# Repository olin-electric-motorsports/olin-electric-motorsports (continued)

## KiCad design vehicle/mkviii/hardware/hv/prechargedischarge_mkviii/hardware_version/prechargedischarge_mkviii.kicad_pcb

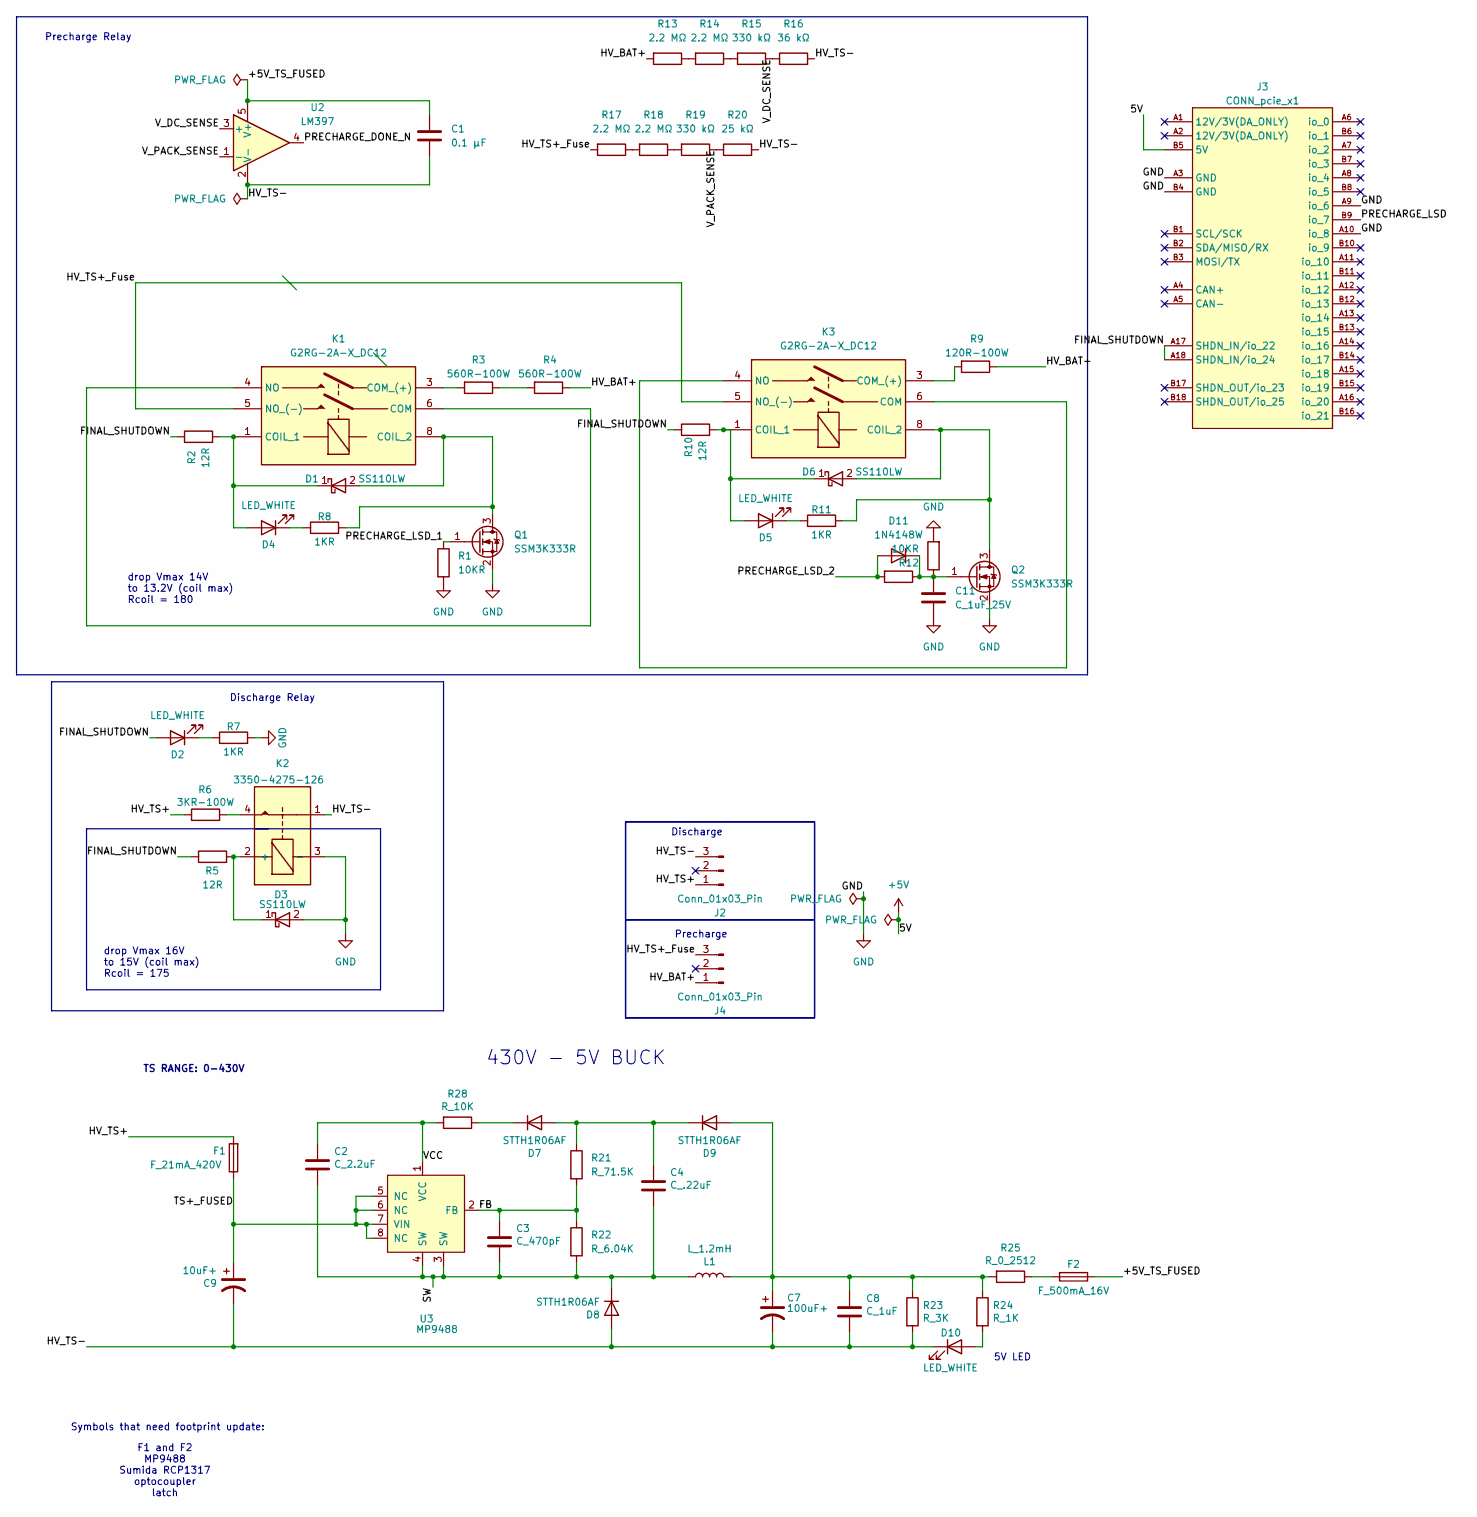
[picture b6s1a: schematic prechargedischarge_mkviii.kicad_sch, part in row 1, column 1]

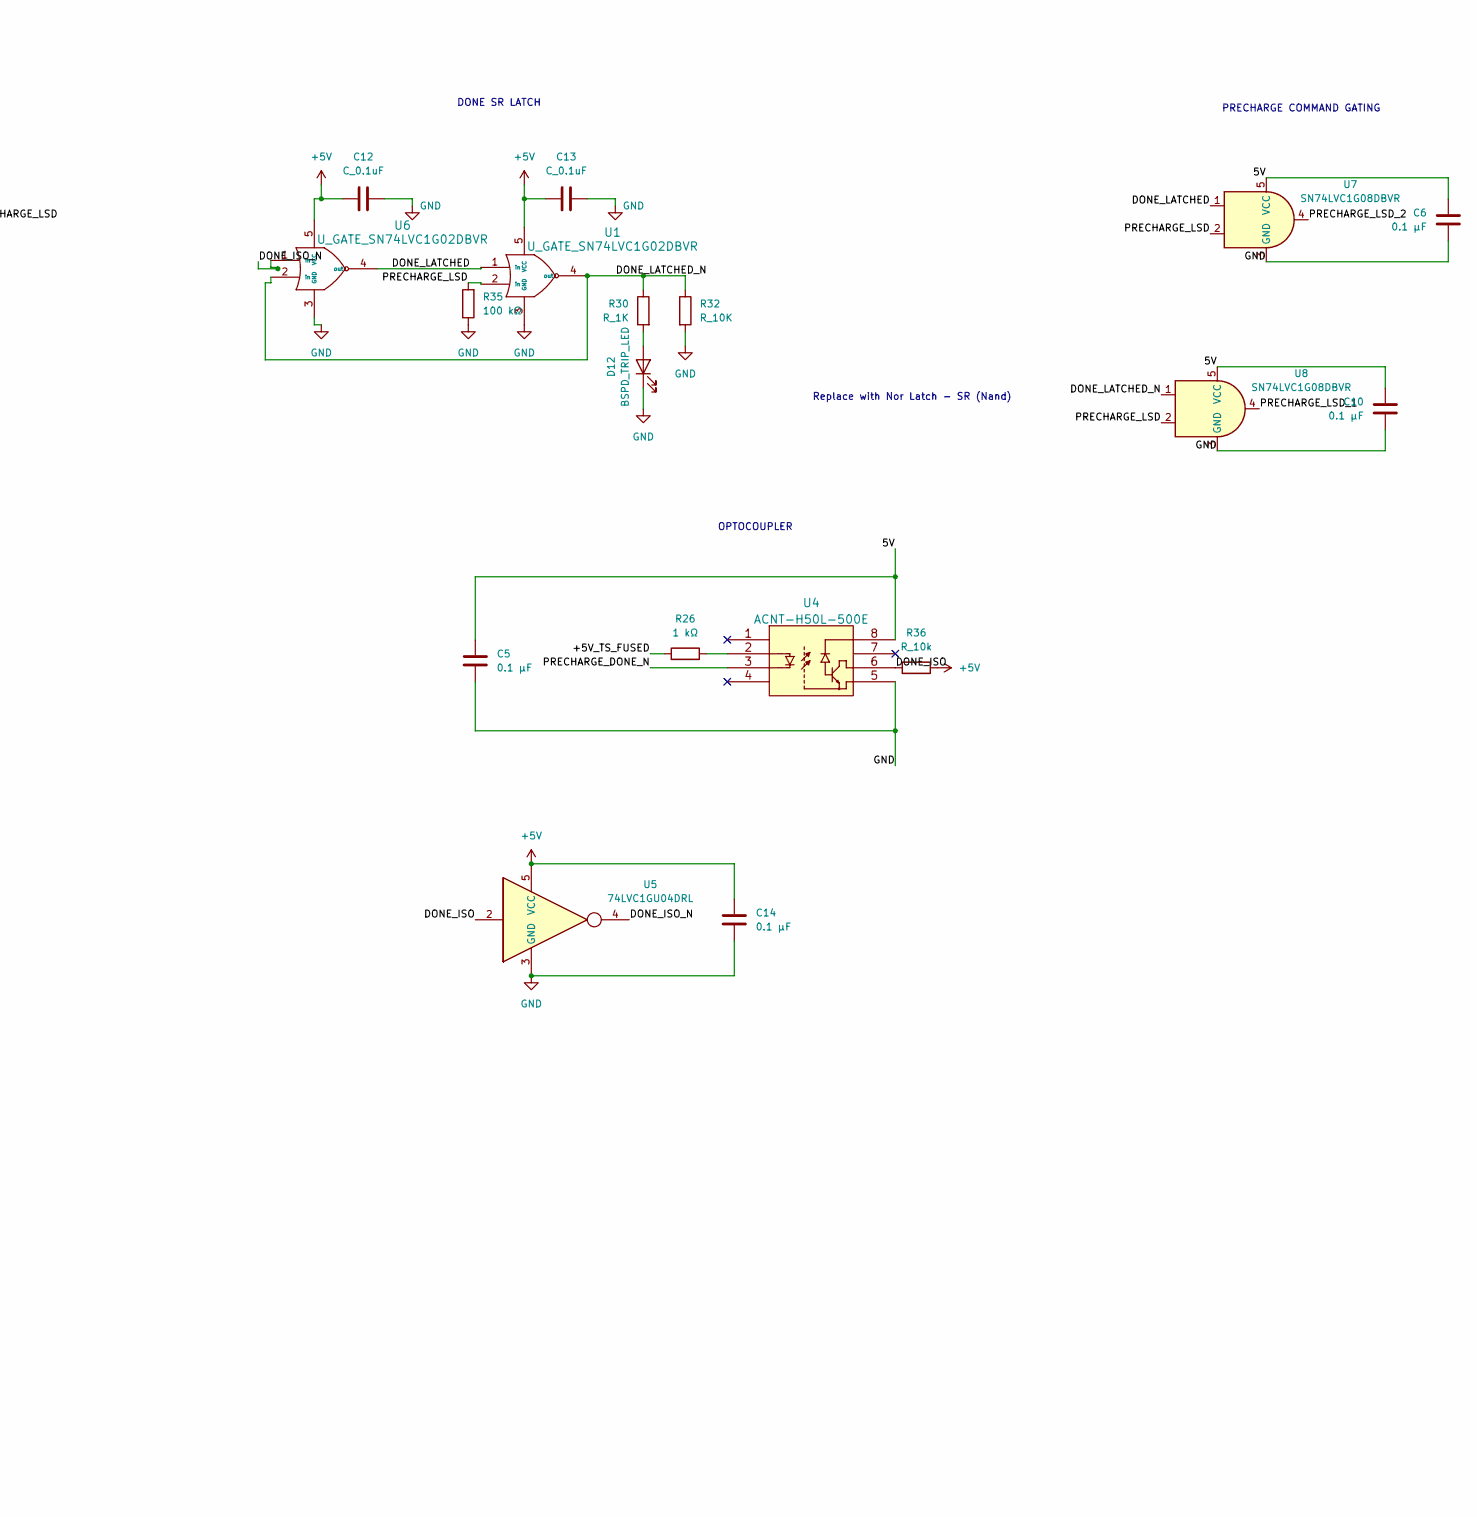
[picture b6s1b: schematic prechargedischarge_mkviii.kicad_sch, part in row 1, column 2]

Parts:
C1, C5, C6, C10, C14: 0.1 µF; C_0603_1608Metric
C2: C_2.2uF; C_0603_1608Metric; MPN GRM188R61E225KA12J
C3: C_470pF; C_0603_1608Metric; MPN 0603B471K500CT
C4: C_.22uF; C_0603_1608Metric; MPN CL10A224KB8NNNC
C7: 100uF+; CP_Radial_D8.0mm_P3.50mm; MPN ESK107M050AG3EA
C8: C_1uF; C_0603_1608Metric; MPN CL10B105KA8NNNC
C9: 10uF+; CP_Radial_D10.0mm_P5.00mm; MPN 450BXC10MEFC10X20
C11: C_1uF_25V; C_0603_1608Metric; MPN CL10B105KA8NNNC
C12, C13: C_0.1uF; C_0603_1608Metric; MPN CL10B104KB8NNWC
D1, D3, D6: SS110LW; D_SOD-123; MPN SS110LW
D2, D4, D5: LED_WHITE; D_0805_2012Metric; MPN B1701TW--20P000314U1930
D7, D9: STTH1R06AF; D_SMA; MPN STTH1R06AF
D8: STTH1R06AF; D_SOD-128; MPN STTH1R06AF
D10: LED_WHITE; LED_0805_2012Metric; MPN B1701TW--20P000314U1930
D11: 1N4148W; D_SOD-123
D12: BSPD_TRIP_LED; D_0805_2012Metric
F1: F_21mA_420V; MPN B59884C0120A054
F2: F_500mA_16V; Fuse_1210; MPN 0ZCH0050FF2G
J2: Conn_01x03_Pin; Molex_Micro-Fit_3.0_43650-0300_1x03_P3.00mm_Horizontal
J3: CONN_pcie_x1; pcie_x1
J4: Conn_01x03_Pin; Molex_Micro-Fit_3.0_43650-0315_1x03_P3.00mm_Vertical
K1, K3: G2RG-2A-X_DC12; K_Relay_DPST_NO_10A_12V_TH; MPN G2RG-2A-X DC12
K2: 3350-4275-126; Relay_Comus_3350; MPN 3350-4275-126
L1: L_1.2mH; MPN RCP1317NP-122L
Q1, Q2: SSM3K333R; SOT-23F; MPN SSM3K333R,LF
R1, R12: 10KR; R_0603; MPN RMCF0603FT10K0
R2, R10: 12R; R_0603_1608Metric; MPN RC0603FR-0712RL
R3, R4: 560R-100W; R_TO247-Heatsink; MPN AP101560RJ
R5: 12R; R_0603; MPN RC0603FR-0712RL
R6: 3KR-100W; R_TO247-Heatsink; MPN AP1013KJ
R7, R8, R11: 1KR; R_0603; MPN RMCF0603FT1K00
R9: 120R-100W; R_TO247-Heatsink; MPN AP101560RJ
R13, R14, R17, R18: 2.2 MΩ; R_1206_3216Metric
R15, R19: 330 kΩ; R_1206_3216Metric
R16: 36 kΩ; R_1206_3216Metric
R20: 25 kΩ; R_1206_3216Metric
R21: R_71.5K; R_0603_1608Metric; MPN RMCF0603FT71K5
R22: R_6.04K; R_0603_1608Metric; MPN RMCF0603FT6K04
R23: R_3K; R_0603_1608Metric; MPN RC0603FR-103KL
R24, R30: R_1K; R_0603_1608Metric; MPN RMCF0603FT1K00
R25: R_0_2512; R_0603_1608Metric; MPN CR2512-J/-000ELF
R26: 1 kΩ; R_0603_1608Metric
R28, R32: R_10K; R_0603_1608Metric; MPN RMCF0603FT10K0
R31: R_100k; R_0603_1608Metric; MPN RMCF0603FT100K
R35: 100 kΩ; R_0603_1608Metric
R36: R_10k; R_0603_1608Metric; MPN RMCF0603FT10K0
U1, U6: U_GATE_SN74LVC1G02DBVR; SOT-23-5; MPN SN74LVC1G02DBVR
U2: LM397; SOT-23-5
U3: MP9488; SOIC-8_3.9x4.9mm_P1.27mm; MPN MP9488GS-Z
U4: ACNT-H50L-500E; MPN ACNT-H50L-000E
U5: 74LVC1GU04DRL; SOT-553
U7, U8: SN74LVC1G08DBVR; SOT-23-5; MPN SN74LVC1G08DBVR

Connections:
+5V: C5.1, C6.1, C10.1, C12.1, C13.1, C14.1, J3.B5 (5V), R36.2, U1.5 (VCC), U4.8, U5.5 (VCC), U6.5 (VCC), U7.5 (VCC), U8.5 (VCC)
/+5V_TS_FUSED: C1.1, F2.1, R26.1, U2.5 (V+)
/DONE_ISO: R36.1, U4.6, U5.2
/DONE_ISO_N: U5.4, U6.1 (in)
/DONE_LATCHED: U1.1 (in), U6.4 (out), U7.1
/DONE_LATCHED_N: R30.1, R32.1, U1.4 (out), U6.2 (in), U8.1
/FB: C3.1, R21.2, R22.1, U3.2 (FB)
/FINAL_SHUTDOWN: D2.2 (A), J3.A17 (SHDN_IN/io_22), J3.A18 (SHDN_IN/io_24), R2.1, R5.1, R10.1
/HV_BAT+: J4.1, R4.1, R9.1, R13.2
/HV_TS+: F1.2, J2.1, R6.1
/HV_TS+_Fuse: J4.3, K1.5 (NO_(-)), K3.5 (NO_(-)), R17.2
/HV_TS-: C1.2, C7.2, C8.2, C9.2, D8.2 (A), D10.1 (K), J2.3, K2.1, R16.2, R20.2, R23.2, U2.2 (V-)
/PRECHARGE_DONE_N: U2.4, U4.3
/PRECHARGE_LSD: J3.B9 (io_7), R35.2, U1.2 (in), U7.2, U8.2
/PRECHARGE_LSD_1: Q1.1 (G), R1.1, U8.4
/PRECHARGE_LSD_2: D11.2 (A), R31.2, U7.4
/SW: C2.2, C3.2, C4.2, D8.1 (K), L1.1, R22.2, U3.3 (SW), U3.4 (SW)
/TS+_FUSED: C9.1, F1.1, U3.5 (NC), U3.6 (NC), U3.7 (VIN), U3.8 (NC)
/VCC: C2.1, R28.2, U3.1 (VCC)
/V_DC_SENSE: R15.1, R16.1, U2.3 (+)
/V_PACK_SENSE: R19.1, R20.1, U2.1 (-)
GND: C5.2, C6.2, C10.2, C11.2, C12.2, C13.2, C14.2, D3.2 (A), D12.1 (K), J3.A3 (GND), J3.A9 (io_6), J3.A10 (io_8), J3.B4 (GND), K2.3 (-), Q1.2 (S), Q2.2 (S), R1.2, R7.2, R12.2, R32.2, R35.1, U1.3 (GND), U4.5, U5.3 (GND), U6.3 (GND), U7.3 (GND), U8.3 (GND)
unnamed: D1.2 (A), K1.8 (COIL_2), Q1.3 (D), R8.2
unnamed: D1.1 (K), D4.2 (A), K1.1 (COIL_1), R2.2
unnamed: D2.1 (K), R7.1
unnamed: D3.1 (K), K2.2 (+), R5.2
unnamed: D4.1 (K), R8.1
unnamed: D5.2 (A), D6.1 (K), K3.1 (COIL_1), R10.2
unnamed: D5.1 (K), R11.1
unnamed: D6.2 (A), K3.8 (COIL_2), Q2.3 (D), R11.2
unnamed: C4.1, D7.2 (A), D9.1 (K), R21.1
unnamed: D7.1 (K), R28.1
unnamed: C7.1, C8.1, D9.2 (A), L1.2, R23.1, R24.1, R25.2
unnamed: D10.2 (A), R24.2
unnamed: C11.1, D11.1 (K), Q2.1 (G), R12.1, R31.1
unnamed: D12.2 (A), R30.2
unnamed: F2.2, R25.1
unnamed: K1.4 (NO), K1.6 (COM)
unnamed: K1.3 (COM_(+)), R3.2
unnamed: K2.4, R6.2
unnamed: K3.4 (NO), K3.6 (COM)
unnamed: K3.3 (COM_(+)), R9.2
unnamed: R3.1, R4.2
unnamed: R13.1, R14.2
unnamed: R14.1, R15.2
unnamed: R17.1, R18.2
unnamed: R18.1, R19.2
unnamed: R26.2, U4.2

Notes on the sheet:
drop Vmax 14V to 13.2V (coil max) Rcoil = 180
Replace with Nor Latch - SR (Nand)
F1 and F2 MP9488 Sumida RCP1317 optocoupler latch
OPTOCOUPLER
Discharge
430V - 5V BUCK
TS RANGE: 0-430V
Discharge Relay
drop Vmax 16V to 15V (coil max) Rcoil = 175
5V LED
Precharge
Precharge Relay
DONE SR LATCH
Symbols that need footprint update:
PRECHARGE COMMAND GATING

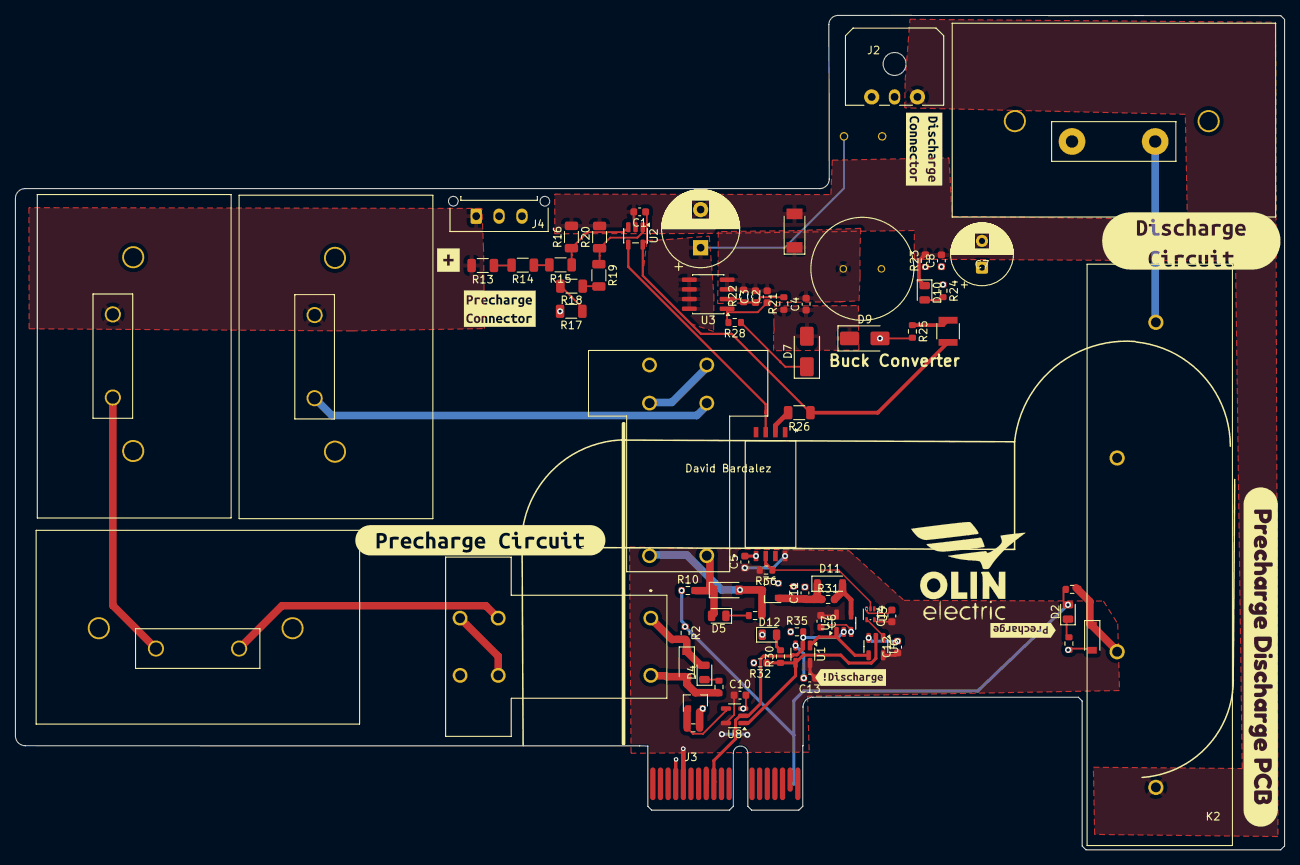
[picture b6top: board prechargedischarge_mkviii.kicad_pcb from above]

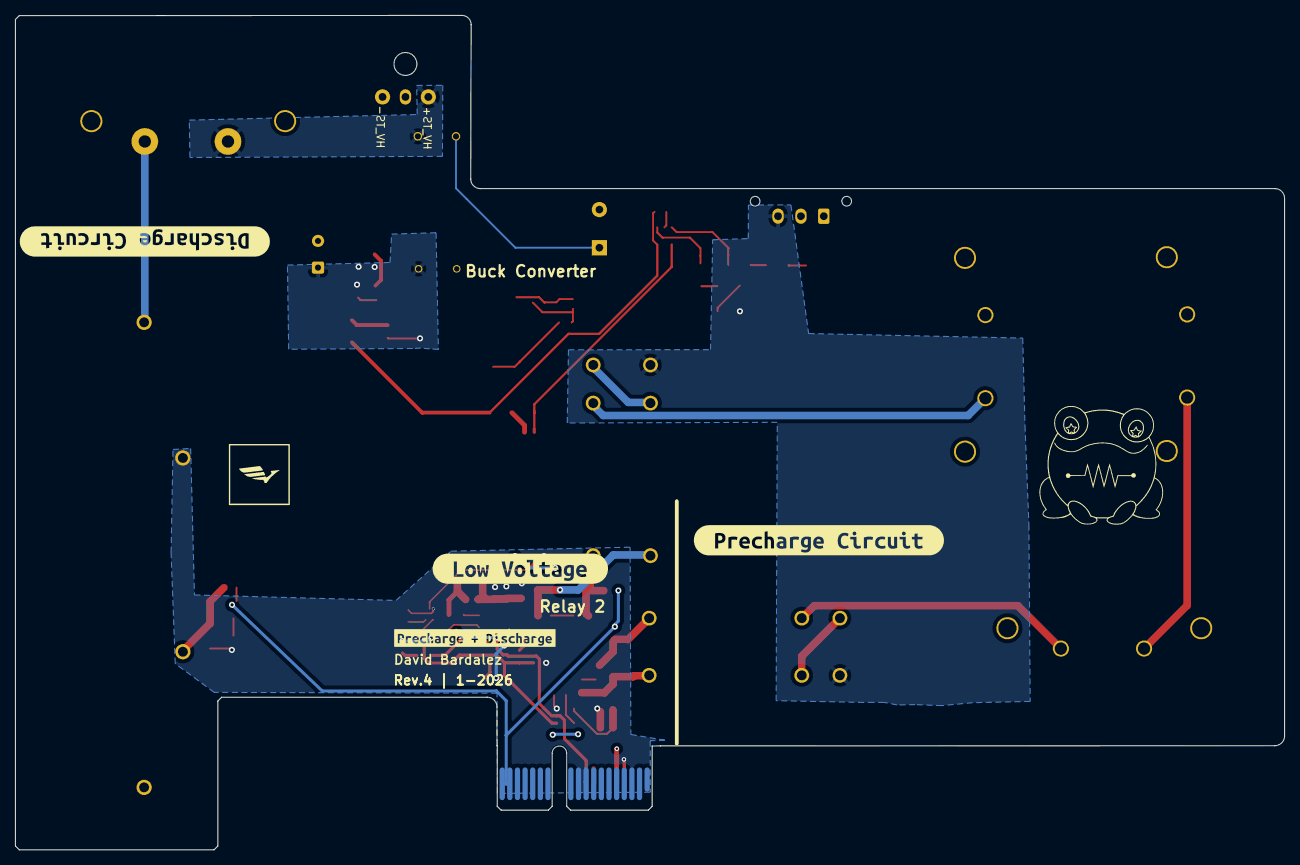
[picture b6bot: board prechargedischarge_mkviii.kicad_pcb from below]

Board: 2 copper layers, 166.4 x 109.4 mm, 90 parts (4 on the bottom side), 48 nets.

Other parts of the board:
kibuzzard-679E7E49, kibuzzard-679E7E49#2: G***; kibuzzard-679E7E49
kibuzzard-679E7E71: G***; kibuzzard-679E7E71
kibuzzard-679E7EA1: G***; kibuzzard-679E7EA1
kibuzzard-679E816B: G***; kibuzzard-679E816B
kibuzzard-679E8163: G***; kibuzzard-679E8163
kibuzzard-679E8270: G***; kibuzzard-679E8270
kibuzzard-679EBF0B, kibuzzard-679EBF0B#2: G***; kibuzzard-679EBF0B
kibuzzard-6784D6A3: G***; kibuzzard-6784D6A3
kibuzzard-6784D6E2: G***; kibuzzard-6784D6E2
kibuzzard-6784D698: G***; kibuzzard-6784D698
kibuzzard-639639B8: G***; kibuzzard-639639B8

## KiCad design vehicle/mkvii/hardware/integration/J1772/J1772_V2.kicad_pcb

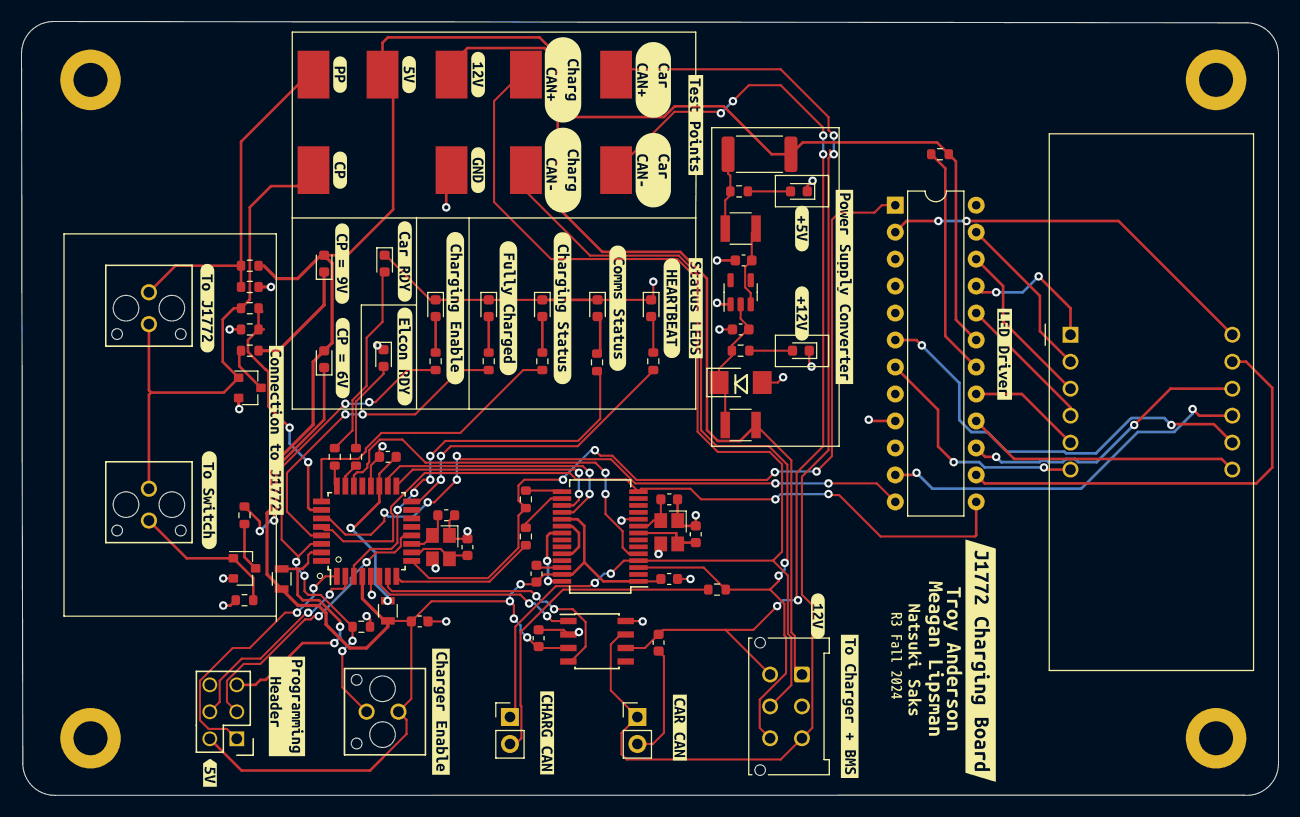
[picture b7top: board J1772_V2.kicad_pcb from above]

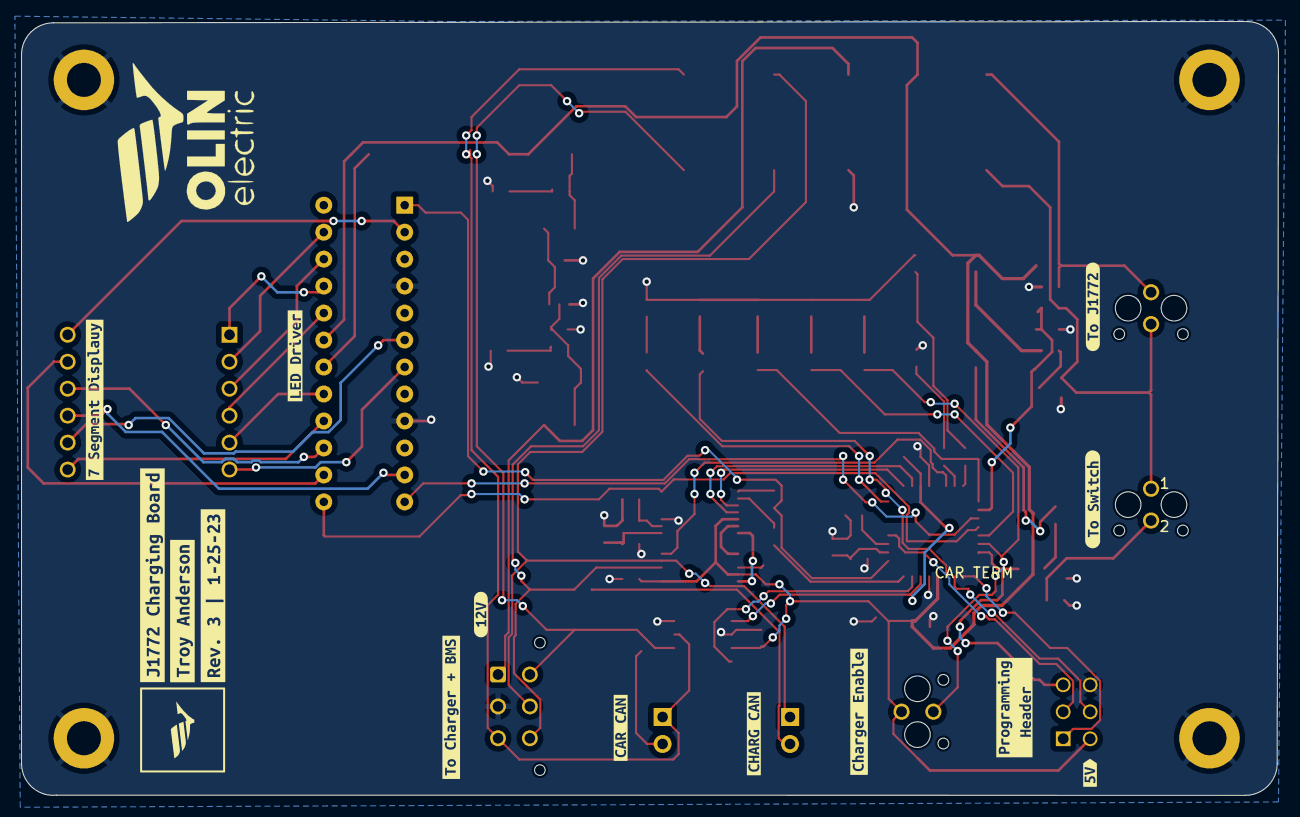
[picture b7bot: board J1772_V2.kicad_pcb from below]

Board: 2 copper layers, 118.4 x 72.9 mm, 129 parts (14 on the bottom side), 71 nets.

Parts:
C1, C5, C9, C11: C_0.1uF; C_0603_1608Metric
C2: C_100pF; C_0603_1608Metric
C3, C4, C12, C13: C_30pF; C_0603_1608Metric
C7, C8: C_1uF; C_0603
D1, D2, D4, D5, D6, D7: WHITE; LED_0603_1608Metric
D3: SMBJ5355B-TP; DO-214AA
D10: CAN Status; LED_0603_1608Metric
D13: On/Off; LED_0603_1608Metric
D14: SPI Status; LED_0603_1608Metric
D16: Charging Status; LED_0603_1608Metric
D17: Fully Charged Status; LED_0603_1608Metric
F1, F2: F_500mA_16V; Fuse_1210
J1, J2, J5: MicroFit_V_2
J3: CONN_02x03; Pin_Header_Straight_2x03
J4, J6: CONN_01x02; PinHeader_1x02_P2.54mm_Vertical
Q2, Q3: SSM3K333R; SOT-23F
R1: R_100; R_0805_OEM
R2: R_10K; R_0805_OEM
R3, R14: R_120; R_0603_1608Metric
R4, R9, R17, R19, R20, R21, R23, R24, R29: R_1K; R_0603
R5, R15, R16: R_330; R_0603
R6: R_2.2K; R_0603
R7: R_1.43K; R_0603
R8: R_1.91K; R_0603
R10: 1KR; R_0603
R11: R_0_2512; R_2512_6332Metric
R12, R13: R_500; R_0603_1608Metric
R18: R_10K; R_0603
R26: R_9.53k; R_0603
TP1, TP2, TP4: TP; Test_Point_SMD
TP3, TP6, TP7, TP8: TP_SMD; Test_Point_SMD
TP5, TP9: Test_Point_SMD
U1: ATMEGA16M1; TQFP-32_7x7mm_Pitch0.8mm
U2: TLV70450DBVR; SOT-23-5
U3: MicroFit_VT_6
U4: SSOP-28_5.3x10.2mm_P0.65mm
U5: CC56-12SEKWA; CA56-12SEKWA
U6: MCP2561-E_SN; SOIC-8_3.9x4.9mm_Pitch1.27mm_OEM
U8: MAX7219; DIP-24_W7.62mm
Y1: Crystal_SMD; Crystal_SMD_FA238
Y2: Crystal_SMD_FA238
kibuzzard-67835F9D, kibuzzard-67835F9D#2: G***; kibuzzard-67835F9D
kibuzzard-67835FD7, kibuzzard-67835FD7#2: G***; kibuzzard-67835FD7
kibuzzard-67840CB0: G***; kibuzzard-67840CB0
kibuzzard-67840D37: G***; kibuzzard-67840D37
kibuzzard-67840D66: G***; kibuzzard-67840D66
kibuzzard-67840EDC: G***; kibuzzard-67840EDC
kibuzzard-67840EE8: G***; kibuzzard-67840EE8
kibuzzard-67840F1B: G***; kibuzzard-67840F1B
kibuzzard-67840F2F: G***; kibuzzard-67840F2F
kibuzzard-67840F06, kibuzzard-67840F06#2: G***; kibuzzard-67840F06
kibuzzard-67841E3C: G***; kibuzzard-67841E3C
kibuzzard-67841ED5: G***; kibuzzard-67841ED5
kibuzzard-67841EE2: G***; kibuzzard-67841EE2
kibuzzard-67841F4B: G***; kibuzzard-67841F4B
kibuzzard-67841F17, kibuzzard-67841F17#2: G***; kibuzzard-67841F17
kibuzzard-67844CA1: G***; kibuzzard-67844CA1
kibuzzard-67844CCD: G***; kibuzzard-67844CCD
kibuzzard-67844CDF: G***; kibuzzard-67844CDF
kibuzzard-678410D5: G***; kibuzzard-678410D5
kibuzzard-678410E4: G***; kibuzzard-678410E4
kibuzzard-678411D3: G***; kibuzzard-678411D3
kibuzzard-678416CB, kibuzzard-678416CB#2: G***; kibuzzard-678416CB
kibuzzard-678416ED, kibuzzard-678416ED#2: G***; kibuzzard-678416ED
kibuzzard-678420E8: G***; kibuzzard-678420E8
kibuzzard-678437FE: G***; kibuzzard-678437FE
kibuzzard-678464B2: G***; kibuzzard-678464B2
kibuzzard-678464BD: G***; kibuzzard-678464BD
kibuzzard-678464CF: G***; kibuzzard-678464CF
kibuzzard-6783604D: G***; kibuzzard-6783604D
kibuzzard-6783617B: G***; kibuzzard-6783617B
kibuzzard-6784104C: G***; kibuzzard-6784104C
kibuzzard-6784174A, kibuzzard-6784174A#2: G***; kibuzzard-6784174A
kibuzzard-6784204A: G***; kibuzzard-6784204A
kibuzzard-67836162: G***; kibuzzard-67836162
kibuzzard-67841056: G***; kibuzzard-67841056
kibuzzard-67841166: G***; kibuzzard-67841166
kibuzzard-67841717, kibuzzard-67841717#2: G***; kibuzzard-67841717
kibuzzard-67843813: G***; kibuzzard-67843813
kibuzzard-67843835: G***; kibuzzard-67843835
kibuzzard-67843848, kibuzzard-67843848#2: G***; kibuzzard-67843848
kibuzzard-67843906: G***; kibuzzard-67843906
kibuzzard-67843917: G***; kibuzzard-67843917
kibuzzard-67843929: G***; kibuzzard-67843929
kibuzzard-67844677: G***; kibuzzard-67844677

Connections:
+5V: C1.1, C5.1, C9.2, C11.1, D1.2 (A), D2.2 (A), J3.2, J5.1, R1.1, R2.1, R5.1, R11.1, R26.1, TP4.1, U1.4 (VCC), U4.1 (VIO), U4.19 (VDD), U4.27 (VDDA), U6.3 (VDD), U8.19 (V+)
+12V: F2.1, TP1.1, U3.1
/CAN_RX: U1.7 ((PCINT11/T1/ICP1B/RXCAN)PC3), U6.4 (RXD)
/CAN_Status: R17.1, U1.16 ((PCINT2/ADC5/INT1/ACMPN0)PB2)
/CAN_TX: U1.6 ((PCINT10/T0/TXCAN)PC2), U6.1 (TXD)
/CAR_CAN_+: J6.1, TP3.1, U3.3, U6.7 (CANH)
/CAR_CAN_-: R3.2, TP9.1, U3.4, U6.6 (CANL)
/CHARGER_CAN_+: J4.1, TP6.1, U3.5, U4.4 (CANH)
/CHARGER_CAN_-: R14.2, TP8.1, U3.6, U4.3 (CANL)
/CHARGER_CS: U1.17 ((PCINT12/ADC8/ACMPN3/AMP1-)PC4), U4.17 (~CS)
/CHARGER_RESET: U1.18 ((PCINT13/ADC9/ACMP3/AMP1+)PC5), U4.18 (~RESET)
/CHARGER_STBY: U1.22 ((PCINT14/ADC10/ACMP1)PC6), U4.5 (STBY)
/Charging_ON/OFF_Status: J5.2, R18.2, R20.1, U1.30 ((PCINT8/INT3/PSCOUT1A)PC0)
/Charging_Status: R23.1, U1.25 ((PCINT15/D2A/AMP2+)PC7)
/DIG_0: U5.12 (CC1), U8.2 (DIG_0)
/DIG_1: U5.9 (CC2), U8.11 (DIG_1)
/DIG_2: U5.8 (CC3), U8.6 (DIG_2)
/DIG_3: U5.6 (CC4), U8.7 (DIG_3)
/EVSE PWM: R8.2, R9.1, U1.26 ((PCINT5/ADC6/INT2/ACMPN1/AMP2-)PB5)
/Fully_Charged_Status: R24.1, U1.29 ((PCINT16/PSCOUT0A)PD0)
/LED_CS: U1.27 ((PCINT6/ADC7/PSCOUT1B)PB6), U8.12 (LOAD)
/MISO: J3.1, U1.1 ((PCINT18/PSCIN2/OC1A/MISO_A)PD2)
/MISO_CAN: R12.1, U1.8 ((PCINT0/MISO/PSCOUT2A)PB0)
/MOSI: J3.4, U1.2 ((PCINT19/TXD/TXLIN/OC0A/~SS/MOSI_A)PD3)
/MOSI_CAN: R13.1, U1.9 ((PCINT1/MOSI/PSCOUT2B)PB1), U8.1 (DIN)
/RESET: J3.5, R2.2, U1.31 ((PCINT24/OCD/~RESET)PE0)
/SCK: J3.3, U1.12 ((PCINT20/ADC1/RXD/RXLIN/ICP1A/SCK_A)PD4)
/SCK_CAN: U1.28 ((PCINT7/ADC4/SCK/PSCOUT0B)PB7), U4.14 (SCK), U8.13 (CLK)
/SPI_Status: R21.1, U1.3 ((PCINT9/PSCIN1/OC1B/~SS_A)PC1)
/control_pilot: J1.2, J2.1, Q3.1 (G), R8.1, TP7.1
/proximity_pilot: J1.1, R5.2, R6.1, TP2.1
GND: C1.2, C2.2, C3.2, C4.2, C5.2, C7.2, C8.2, C9.1, C11.2, C12.1, C13.2, D3.2 (A), D4.1 (K), D5.1 (K), D6.1 (K), D7.1 (K), D10.1 (K), D13.1 (K), D14.1 (K), D16.1 (K), D17.1 (K), J3.6, Q2.2 (S), Q3.2 (S), R6.2, R7.2, R9.2, R18.1, TP5.1, U1.5 (GND), U1.20 (AGND), U2.1 (GND), U3.2, U4.10 (GND), U4.26 (VSS), U6.2 (VSS), U6.8 (STBY), U8.4 (GND), U8.9 (GND), Y1.2, Y1.4, Y2.2, Y2.4
unnamed: D1.1 (K), R16.1
unnamed: D2.1 (K), R15.1
unnamed: C7.1, D3.1 (K), F2.2, R4.1, U2.2 (VI)
unnamed: D4.2 (A), R4.2
unnamed: D5.2 (A), R10.2
unnamed: D6.2 (A), R19.2
unnamed: D7.2 (A), R29.2
unnamed: D10.2 (A), R17.2
unnamed: D13.2 (A), R20.2
unnamed: D14.2 (A), R21.2
unnamed: D16.2 (A), R23.2
unnamed: D17.2 (A), R24.2
unnamed: F1.2, R10.1, R11.2
unnamed: J4.2, R14.1
unnamed: J6.2, R3.1
unnamed: Q2.3 (D), R15.2
unnamed: J2.2, Q2.1 (G), R7.1
unnamed: Q3.3 (D), R16.2
unnamed: R19.1, U1.23 ((PCINT3/AMP0-)PB3)
unnamed: R29.1, U1.24 ((PCINT4/AMP0+)PB4)
unnamed: C4.1, U1.10 ((PCINT25/OC0B/XTAL1)PE1), Y1.3
unnamed: C3.1, U1.11 ((PCINT26/ADC0/XTAL2)PE2), Y1.1
unnamed: C2.1, R1.2, U1.19 (AVCC)
unnamed: C8.1, F1.1, U2.3 (VO)
unnamed: C12.2, U4.9 (OSC1), Y2.1
unnamed: C13.1, U4.8 (OSC2), Y2.3
unnamed: U4.21 (RxCAN), U4.28 (RXD)
unnamed: R13.2, U4.15 (SI)
unnamed: R12.2, U4.16 (SO)
unnamed: U4.20 (TxCAN), U4.24 (TXD)
unnamed: U5.3 (DPX), U8.22 (SEG_DP)
unnamed: U5.11 (a), U8.14 (SEG_A)
unnamed: U5.7 (b), U8.16 (SEG_B)
unnamed: U5.4 (c), U8.20 (SEG_C)
unnamed: U5.2 (d), U8.23 (SEG_D)
unnamed: U5.1 (e), U8.21 (SEG_E)
unnamed: U5.10 (f), U8.15 (SEG_F)
unnamed: U5.5 (g), U8.17 (SEG_G)
unnamed: R26.2, U8.18 (ISET)

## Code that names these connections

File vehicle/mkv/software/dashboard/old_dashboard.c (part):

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//spi
#define CS_DDR DDRC
#define CS_PORT PORTC
#define CS_PIN PC4

// LEDs
#define DEBUG_LED1                         PB5
#define DEBUG_LED2                         PB6

#define PORT_DEBUG_LED1                    PORTB
#define PORT_DEBUG_LED2                    PORTB

#define RJ_LED1                            PC0
#define RJ_LED2                            PC1

#define PORT_RJ_LED1                       PORTC
#define PORT_RJ_LED2                       PORTC

#define BRAKE_LED                          PB2
#define LV_LED                             PD6
#define HV_LED                             PD7

#define PORT_BRAKE_LED                     PORTB
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#define PORT_HV_LED                        PORTD

// BMS and IMD Button Lights
#define BMS_LED                            PD0
#define PORT_BMS_LED                       PORTD

#define IMD_LED                            PB3
#define PORT_IMD_LED                       PORTB

// Start Button Status + LED
#define START_PIN                          PC6
#define PORT_START                         PORTC

#define START_LED                          PB4
#define PORT_START_LED                     PORTB

/* Ready to Drive */
#define RTD_LSD                            PC5
#define RTD_PORT                           PORTC

/* Steering Pot*/
#define STEERING_POT                       PD5
#define PORT_STEERING_POT                  PORTD


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}

/*ISR(PCINT2_vect){
	if(bit_is_set(PIND,PD2)) {
		PORTC |= _BV(PC0);
	}else{
		PORTC &= ~_BV(PC0);
	}
} */

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	//Set pull up resistor for steering pot
	PORT_STEERING_POT |= _BV(STEERING_POT);

	//PORTC |= _BV(PC0);

	/* Setup pin change interrupt registers for start pin*/
	PCICR |= _BV(PCIE1) | _BV(PCIE2);
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
	/*----- Setup PWM output -----*/
	//Output compare pin is OC1B, so we need OCR1B as our counter
	DDRC |= _BV(PC0); //Enable output pin
	DDRC |= _BV(PC1); //Enable output pin

	// DDRD |= _BV(PD3);
	DDRD |= _BV(PD2); //PWM is happening on this pin

	// pg 119 and 110 of datasheet
	// currently running on mode 5 for 8-bit resolution timer
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
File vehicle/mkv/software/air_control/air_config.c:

#include "vehicle/mkv/software/air_control/air_config.h"
#include "libs/gpio/api.h"
#include "libs/gpio/pin_defs.h"
#include "libs/timer/api.h"

/*
 * GPIO pin definitions
 */

gpio_t PRECHARGE_CTL = PB2;
gpio_t AIR_N_LSD = PC6;

// Inputs
gpio_t SS_TSMS = PB3;
gpio_t SS_IMD_LATCH = PB4;
gpio_t SS_MPC = PB5;
gpio_t SS_HVD_CONN = PB6;
gpio_t SS_HVD = PB7;

gpio_t BMS_SENSE = PC0;
gpio_t AIR_P_WELD_DETECT = PC4;

gpio_t IMD_SENSE = PD0;

#ifdef BOARD_HACKERBOARD

gpio_t FAULT_LED = PD6;
gpio_t GENERAL_LED = PD5;
gpio_t AIR_N_WELD_DETECT = PC5;

#else

gpio_t FAULT_LED = PB7;
gpio_t GENERAL_LED = PD6;
gpio_t AIR_N_WELD_DETECT = PC7;

#endif

timer_cfg_s timer0_cfg = {
    .timer = TIMER0,
    .timer0_mode = TIMER0_MODE_CTC,
    .prescalar = CLKIO_DIV_1024,
    .channel_a = {
        .channel = CHANNEL_A,
        .output_compare_match = 244, // 16 Hz
        .pin_behavior = DISCONNECTED,
        .interrupt_enable = true,
        // .interrupt_callback = timer0_isr,
    },
    .timer_overflow_interrupt_enable = false,
};

timer_cfg_s timer1_cfg = {
    .timer = TIMER1,
    .timer1_mode = TIMER1_MODE_CTC,
    .prescalar = CLKIO_DIV_1,
    .channel_a = {
        .channel = CHANNEL_A,
        .output_compare_match = 4000,
        .pin_behavior = DISCONNECTED,
        .interrupt_enable = true,
        // .interrupt_callback = timer1_isr,
    },
    .timer_overflow_interrupt_enable = false,
};

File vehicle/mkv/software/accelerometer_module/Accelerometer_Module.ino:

/*
 * Board: Accelerometer Module
 * Version: v1.0
 * Description: The goal of this board is to measure the frequency of vibrations in the chassis
 * in order to perform modal analysis.
 */

/****** Libraries ******/
#include <SPI.h>
#include <SD.h>
#include <Wire.h>

/****** LED Macros ******/
// Voltage Indicator LED
#define DDR_VLED DDRC
#define PORT_VLED PORTC
#define HIGH_VLED PC2
#define MED_VLED PC1
#define LOW_VLED PC0

// Status LED
#define DDR_SLED DDRD
#define PORT_SLED PORTD
#define ON_LED PD5
#define READY_LED PD6


/****** Button Macros ******/
#define BUTTON PD7
#define DDR_BUTTON DDRD


/****** SPI Macros ******/
#define MOSI PB3
#define MISO PB4
#define SCK PB5
#define DDR_SPI DDRB
#define PORT_SPI PORTB

// Accelerometer
#define ACC_CS PB2

#define READ 1
#define WRITE 0
#define MULTIPLE 1
#define SINGLE 0
#define RWbit 7 // Location of Read/Write Bit (Accelerometer)
#define MSbit 6 // Location of Multiple/Single Bit (Accelerometer)
#define WHOAMI 0x0F // Location if WHO AM I register (Accelerometer)
#define OUT_XL 0b101000 // Location of OUT_X_L (Accelerometer)
#define OUT_XH 0b101001 // Location of OUT_X_H (Accelerometer)
#define OUT_YL 0b101010 // Location of OUT_Y_L (Accelerometer)
#define OUT_YH 0b101011 // Location of OUT_Y_H (Accelerometer)
#define OUT_ZL 0b101100 // Location of OUT_Z_L (Accelerometer)
#define OUT_ZH 0b101101 // Location of OUT_Z_H (Accelerometer)

// SD Card
#define SD_CS PB1

/****** I2C Macros ******/
#define INA260_ADDR 1000000
#define VOLTAGE_REG 0x02

// Variable Declaration

void setup() {
  
  DDR_SLED |= _BV(READY_LED);
  DDR_BUTTON &= ~_BV(BUTTON);
  DDR_VLED |= _BV(HIGH_VLED);

  // Accelerometer CS Pin
  DDR_SPI |= _BV(ACC_CS);

  // Activate SD Card @ CS Pin
  // TODO: Check if PB1 can be used a select pin input for .begin() function
  SD.begin(SD_CS);

  // Activate I2C Communication
  Wire.begin();

  // Set SPI pins at Output
  DDR_SPI |= _BV(SCK) | _BV(MOSI);

  
//  PCICR |= _BV(PCIE2);
//  PCMSK2 |= _BV(PCINT23);
//  sei();
}

//ISR(PCINT2_vect) {
//  PORTD ^= _BV(PD6);
//}

void loop() {
  int xyzData[6]; // initalize memset

  // QUESTION: Do I need this if I initalize the variable in every loop?
  memset(xyzData,0,6); // set xyzData to zeros

  // get accelerometer data
  for (int i = 0; i < 6; i++) {
    xyzData[ i ] = getData(READ, SINGLE, (OUT_XL + i), ACC_CS);
  }

  // creates/opens file "data.txt"
  // starts writing at END of file
  File data = SD.open("data.txt", FILE_WRITE);
  if (data) {
    for ( int i = 0; i < 3; i++ ) {
      data.println(xyzData[ i*2 ] >> 6 | xyzData[ (i*2)+1 ] << 2);
    }
    data.println("");
    data.close();
  }
  
  // I2C Slave Address (INA260) -- 1000000
  // Bus Voltage register (0x02)
  // Alert Limit register (0x07)
  Wire.beginTransmission(INA260_ADDR);
  Wire.write(byte(VOLTAGE_REG));
  Wire.endTransmission();
  Wire.requestFrom(INA260_ADDR, 16);
  int voltage = 0b0;
  while (Wire.available()) {
    int data = Wire.read();
    // Will the data come in the right order to collect it like this?
    voltage = (voltage << 1) | data;
  }
  
  if (bit_is_set( PINB, PB1 )) {
    PORT_SLED ^= _BV(READY_LED);
    delay(1000);
  }
}

int getData(int rwbit, int msbit, int address, int cs) {
  // Accelerometer Datasheet - Max Speed 1MHz
  // Page 27 - SPI MODE 0 - Output on Falling Edge, Data Capture on Rising Edge
  
  SPI.beginTransaction(SPISettings(400000, MSBFIRST, SPI_MODE0));
  PORT_SPI &= ~_BV(cs);
  int output = SPI.transfer(rwbit << RWbit | msbit << MSbit | address);
  PORT_SPI |= _BV(cs);
  SPI.endTransaction();
  return output;
}

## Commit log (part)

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2024-09-30 Add decoder py_binary target, update examples
2024-09-30 Add Can Print (#282)
    * Add can_print files from drew/imu-code
    * Finish multi arg input
    * Add decoder progress
    * Complete decoder, needs further dbg
    * Add most examples, dynamic negative broken
    * Debug examples
2024-09-30 add python install command to readme (#292)
2024-09-30 Revert "Add Can Print (#282)" (#293)
    This reverts commit 3d914c7d35ab503f9a63e993c16ba730811a55a5.
2024-10-01 Add dummy change for running CI on main
2024-10-01 fmt bazel files
2024-10-01 Update path
2024-10-01 Add bazel cache back in
2024-10-01 added STM schematic and created ARCHIVE file for incomplete projects
2024-10-01 Revert "Merge branch 'drew/fix-ci' into drew/imu-code"
    This reverts commit 891f81c5d79381f63d19ad1db9c0ae7663e0baac.
2024-10-03 rename
2024-10-03 add new mcu
2024-10-03 remove legacy can print files, calls to can print
2024-10-04 remove comment step in kicad ci
2024-10-04 temp remove bazel cache
2024-10-04 remove broken build
2024-10-04 comment out debug build for ci
2024-10-04 add arb id and deocoder docs
2024-10-04 complete support for alt/main spi bus selection
2024-10-05 update various parts
2024-10-05 Move icm20948 lib to vehicle/common
2024-10-05 add todo for keeping track of the active register bank
2024-10-05 remove old variable
2024-10-05 update timer hz comment
2024-10-06 add standard 0603 leds
2024-10-07 updated hole size for pressfit and removed merge conflicts (ff to new stuff!)
2024-10-07 updated hole size for pressfit and removed merge conflicts (ff to new stuff!) (#296)
2024-10-07 Update bspd.h to include pin change for 5kW led (bodge to get ready for comp) (#297)
2024-10-10 Update README.md (cantools install) (#298)
2024-10-13 finish sch
2024-10-13 resolve erc, associate all parts
2024-10-14 re-built the OEM parts library to include new parts for this year, delete old parts we don't use, and migrate older parts from the 'formula' lib That took a really long time, phew.
2024-10-14 re-built the OEM parts library to include new parts for this year, delete old parts we don't use, and migrate older parts from the 'formula' lib (#300)
    That took a really long time, phew.
2024-10-14 Update README.md to add more info on kicad setup (#301)
2024-10-16 place all components
2024-10-17 fix oem library
2024-10-17 Project for wheel speed board
2024-10-18 initial design of power+thermistor board
2024-10-18 Deleted jacobtest.py (temporary file) and added radio_test.py
2024-10-22 BSPD Schematics Update
2024-10-23 BSPD Schmatics Update v2 (with 10-22-2024 revisions from Ian Walsh)
2024-10-24 Deleted old telemetry board files. Moved current telemetry code into proper directory
2024-10-25 finished dashboard schematic
2024-10-26 bms core schematic and core updates
2024-10-29 one trace was wonky
2024-11-01 remove btldr to make space for cell balancing
2024-11-01 remove unused variable
2024-11-01 update deps in build files
2024-11-01 add conditional for enabling/disabling balalncing
2024-11-01 find lowest voltage, cell, segment
2024-11-01 balancing without disturbing voltage readings
2024-11-01 confirm balancing on each cell
2024-11-03 only discharge cells outside of a range of the lowest voltage cell
2024-11-03 Added can messages for temp status
    UPdated yml and temp task with added status can messages
2024-11-04 check fault state before balancing
2024-11-04 update for uint16_t
2024-11-05 Updated connector schematic
2024-11-05 Finished everything but voltage filtering
2024-11-05 tweaked some traces with revised edge cuts
2024-11-05 Updated layout
2024-11-06 make grounds face downwards, also fixed groun locations
2024-11-06 Debugging session with Ayush
2024-11-06 Creating new motherboard file, putting it in mkvii
2024-11-07 Completed layout version 1
2024-11-08 FinalBMS
2024-11-08 Fixed to 4 mux outputs
2024-11-08 Changing display names
2024-11-08 Final PCB Design with Beans Logo
2024-11-08 update for 6 segments
2024-11-08 Updated TSAL/AIL to meet new rules
2024-11-08 putting everything in hierarchical sheets
2024-11-09 Finished cleaning up silkscreen and traces
2024-11-09 Removed I2C PU resistors bc already on DA board
2024-11-12 reorganized schematic entirely, color coded connection types, connected hierarchical sheets
2024-11-13 Saving DA board
2024-11-14 Initial attempt for profiling temp
    implemented extract_enum_value to get the value from bytes and
    printing the can messages
2024-11-14 Added data storage
2024-11-21 Added LV Motherboard Files
2024-11-22 added sensing logo
2024-11-23 Add wheel speed board
2024-11-24 INitial design
2024-11-24 Fixed DRC issues
2024-11-25 Updated DA pins and added silkscreen
2024-11-25 Changed trace widths and fixed DRC issues
2024-12-11 PrechargeDischarge
2024-12-11 renamed hierarchical sheets to reflect shdn changes, corrected ERC errors and annotated
2024-12-11 changed ail resistors
2024-12-12 Updated main BUILD
2024-12-13 Update for Amanda with new buck converter
2024-12-17 Cleaned up schematics and new PCB layout.
2024-12-18 Changed fuses for buck converter.
2024-12-20 added all board outlines but precharge discharge, positioned connectors
2024-12-23 Update to motherboard schematics and PCB layout. This version is ready to be reviewed by senior engineers.
2024-12-24 removed old buck parts
2024-12-24 updated my parts library and redid buck schematic for readability
2024-12-24 put boards in spots and generally arranged everything; made edits to buck
2024-12-30 realized shdn_to_tsms is not the same as final_shdn
2024-12-30 never mind i had connected shdn_sense_tsms to final_shdn which is correct
2025-01-03 precharge_discharge changes
2025-01-03 imd latch facing down version
2025-01-05 routed HV traces, equalized differential pair lines
2025-01-05 adjusted positioning of all boards, increased tp area, fixed board outline, imported step files
2025-01-07 removed ground plane under HV, added silkscreen hv lv markings
2025-01-07 moved tsal mounting hole and round copper pours slightly
2025-01-08 converting to 4 layer, add power planes, rearrange buck
2025-01-08 improved air control shdn sense routing
2025-01-08 wired LEDs temporarily
2025-01-08 repositioned a few traces
2025-01-09 aligned hv connectors, moved CAN test points, shifted mounting holes
2025-01-22 add unknown changes
2025-01-22 Fix rules_python version
2025-01-22 Updated rules python version
2025-01-25 Hide python venv
2025-01-25 Fix typo in canviewer instructions
2025-01-28 Update gui.py to hide sections when clicking titles
2025-01-29 Added telemetery transmit and recieve code
2025-01-29 Updated telemerty transmit code
2025-01-29 Updated test telemetry rx code
2025-01-30 BSPD Firmware v3 - Preliminary (this is a draft of the BSPD firmware for MKVII); moved BSPD outside Nose Bridge folder
2025-02-01 Revert canserver to pre-telemetry version
2025-02-01 Fix telemetry viewer
2025-02-04 Fixed canviewer for temps and tiny bms code to send can message for temp readings
2025-02-04 Fixed bms.c to read temps
    Configuring all muxes at the start and removed mux iteration
2025-02-08 Fixed canviewer formatting
2025-02-11 Add/Fixed missing dependencies like stdin blah blah by fixing the directory path in the committed files
2025-02-14 Updated capitalization for CAN Variables
2025-02-14 Potential update to gui adding lpms section
2025-02-15 Replaced KiCAD Files with Final FAB KiCAD Files; Changed directory name to bspd
2025-02-21 Bazel fixes for Ubuntu 24
2025-02-21 Created initial display driver files
2025-02-21 bms motherboard final
2025-02-21 rules python fix
2025-02-21 BMS DA hardware final
2025-02-21 BMS power therm board hardware final
2025-02-25 working code :D
2025-03-02 final dashboard firmware files
2025-03-04 This includes changes to the common file, build file in mkii software and a tempurary throttle code for testing
2025-03-04 Tried to get ss_bspd can signal behavior correct
2025-03-04 Change python install
    Change python install from python3 to python 3.10
2025-03-07 add suspension strain firmware
2025-03-07 Initial fault handling fix
2025-03-07 Initial commit for error handling and fixes.
2025-03-07 Added clear fault in open wire
2025-03-08 dashboard files!
2025-03-08 Update display driver test
2025-03-08 Created structure for pdu CAN yml
2025-03-09 BSPD Firmware Version 3 Cleaned Up Code; Moved Var Declarations to .c file; removed unused functions; reverted ss_bspd and BSPD_FAULT led changes
2025-03-09 added all board files and a software structure (NEEDS UPDATES ON THE SOFTWARE SIDE)
2025-03-11 commit draft sus strain firmware
2025-03-12 Initial code for using SPI
2025-03-12 Create init functions for hardware
2025-03-13 Added can print and flipped threshold logic to work with positive numbers
2025-03-24 added software directory for MKVII
2025-03-26 Dashboard is working!
2025-03-26 new motor controller syntax
2025-03-26 flipped polarity on the dashboard input sensing pins
2025-03-28 Add ADC SPI receive
2025-04-01 added can messages in canviewer and can print
2025-04-01 downgrade py version to 3.9
2025-04-01 add fabbed air control files
2025-04-01 trial
2025-04-02 Debugged throttle
2025-04-05 Fix pcint#_callback function issues that caused Shutdown Sense can message irregularities
2025-04-05 Add new spi transcieve function to header file
2025-04-05 Made brake_implausibility_occurred not a static var
2025-04-05 update gpio pins and yml can outputs
2025-04-06 pitch and roll
2025-04-09 Debug attempt
2025-04-10 Charging display debug
2025-04-11 some version of yaw
2025-04-16 Attempt to list all open wire pins for debugging
2025-04-16 Added message and func to parfe uint32 message and display on canviewer
2025-04-16 uncommented set faults
2025-04-16 Attempt to control fan using pwm
2025-04-17 Uncommmented btldr code
2025-04-18 initial attempt to make btldr 64m1 compat
2025-04-18 Fixed can message send logic and canviewer parsing logic
2025-04-19 Fix recieveing CAN
2025-04-20 added __vectors in 64m1 ld
2025-04-20 DCP DISABLED
2025-04-21 Shutdown nodes working
2025-04-22 temp - vol debugging
2025-04-22 TS light fix
2025-04-24 Calibrated Accelerator Pedal Potentiometers
2025-04-25 btld build dynamic for 64m1 and 16m1
2025-04-25 Uncommented can voltage msg
2025-05-02 air control final code
2025-05-02 updated btldr to working version
2025-05-02 bms merging strangeness
2025-05-02 Flipped fan logic and it works!
2025-05-08 Testing current sensing
2025-05-09 Commented out Heartbeat LED Code
2025-05-09 Cooling loop final touches
2025-05-11 updated charging board
2025-05-12 Added Untested Wheel Speed Firmware
2025-06-16 update calibration script
    quite verbose and very messy
2025-06-17 Throttle ADC fault latching fix
2025-06-17 Motor direction and avr version
2025-06-18 Added Jacob Keller's Latest PDU Firmware Version
2025-06-22 Modified Final Version of PDU Firmware to Build Successfully using Bazel
2025-07-22 rough draft of kicad part
2025-07-23 Save initial STM32G441KB pin config
2025-08-20 updates still working on kibot
2025-09-29 Added OEM v2 KiCad Parts Libraries
2025-10-02 Added OEM v2 KiCad Symbols Library
2025-10-02 Moved Symbols Library
2025-10-19 Added PCIe and Ampseal Connectors to KiCad Parts Libraries
2025-11-08 logging imu data
2025-11-09 Update avr version.
2025-11-17 minor changes to remove unnecessary stuff from throttle (still doesn't build)
2025-12-01 Added Precharge-Discharge Relays to Parts Library
2025-12-04 DR2 Version
2025-12-10 Added Various Connectors and Updated Resistors
2025-12-11 finalized firmware version of precharge discharge board(two stage precharge)
2025-12-15 hardware version 1 done
2025-12-18 Added New BMS Connector
2026-01-07 AddedMissing Zener Diode
2026-01-21 adding two wire screw terminal kiCAD schematic and PCB layout to OEM library
2026-02-02 final board for precharge discharge
2026-02-04 Added E-Meter Temperature Sensor to Parts Library.
